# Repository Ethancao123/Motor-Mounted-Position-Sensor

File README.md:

# AS5048B Motor Mount
 AS5048 Breakout PCB for 18XX - 20XX Brushless motors

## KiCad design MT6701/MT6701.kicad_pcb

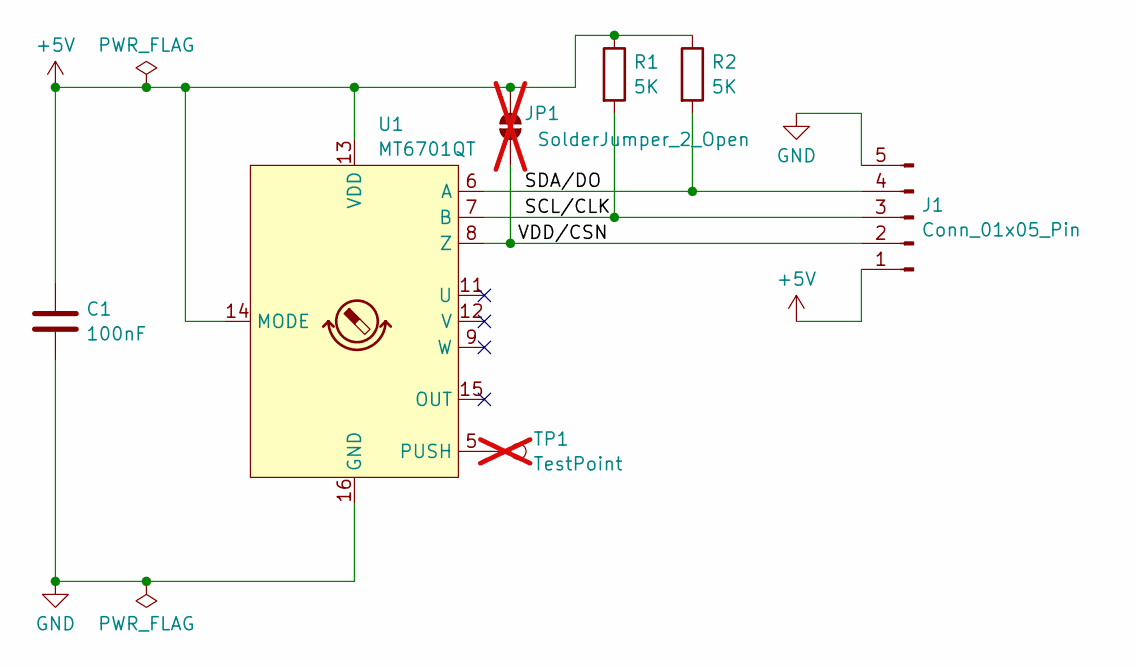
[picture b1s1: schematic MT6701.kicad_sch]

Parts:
C1: 100nF; C_0402_1005Metric; LCSC Part Number C1525
J1: Conn_01x05_Pin; JST_GH_SM05B-GHS-TB_1x05-1MP_P1.25mm_Horizontal; LCSC Part Number C189896
JP1: SolderJumper_2_Open; SolderJumper-2_P1.3mm_Open_TrianglePad1.0x1.5mm; not fitted
R1, R2: 5K; R_0402_1005Metric; LCSC Part Number C25905
TP1: TestPoint; TestPoint_Pad_1.0x1.0mm; not fitted
U1: MT6701QT; QFN-16-1EP_3x3mm_P0.5mm_EP1.7x1.7mm; LCSC Part Number C2913974

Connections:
+5V: C1.1, J1.1, JP1.2 (B), R1.1, R2.1, U1.13 (VDD), U1.14 (MODE)
/SCL/CLK: J1.3, R1.2, U1.7 (B)
/SDA/DO: J1.4, R2.2, U1.6 (A)
/VDD/CSN: J1.2, JP1.1 (A), U1.8 (Z)
GND: C1.2, J1.5, J1.MP, U1.16 (GND), U1.17 (GND)
unnamed: TP1.1, U1.5 (PUSH)

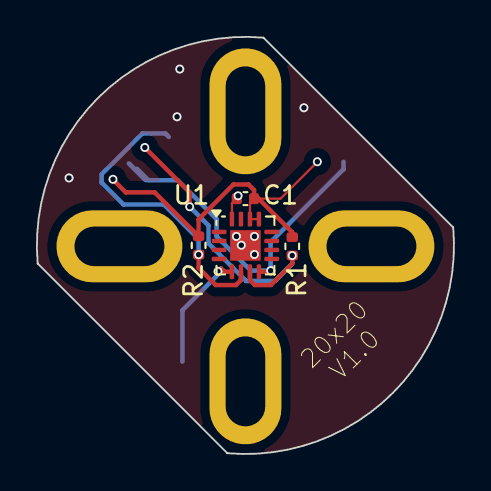
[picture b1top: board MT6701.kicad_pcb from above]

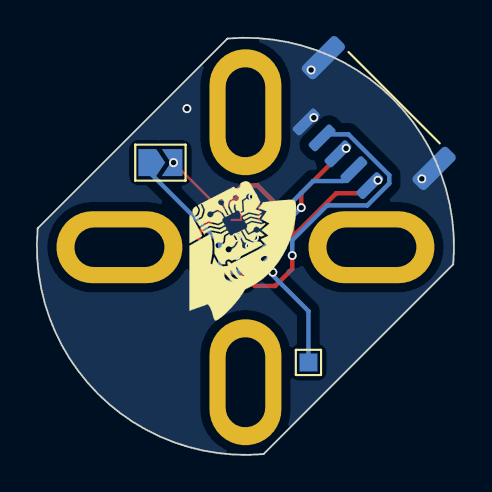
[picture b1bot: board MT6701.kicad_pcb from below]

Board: 2 copper layers, 23.2 x 23.2 mm, 7 parts (3 on the bottom side), 6 nets.

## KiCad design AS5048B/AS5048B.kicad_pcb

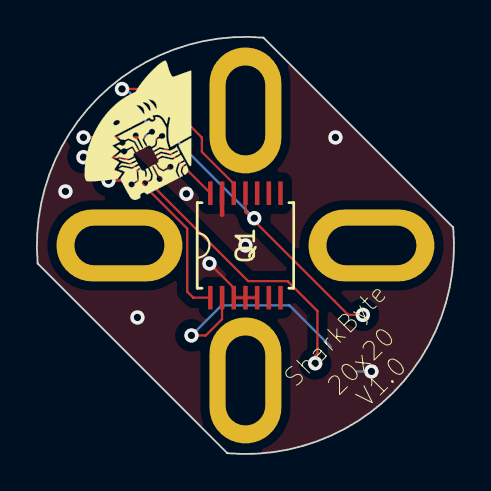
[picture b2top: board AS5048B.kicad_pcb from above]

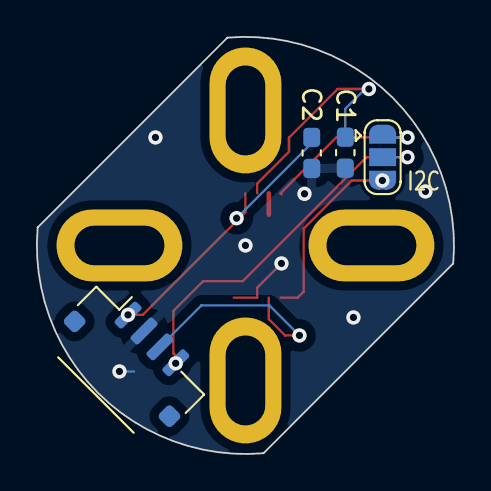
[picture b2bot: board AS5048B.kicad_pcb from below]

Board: 2 copper layers, 23.2 x 23.2 mm, 5 parts (4 on the bottom side), 7 nets.

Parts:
C1: 10uF; C_0603_1608Metric_Pad1.08x0.95mm_HandSolder
C2: 100nF; C_0603_1608Metric_Pad1.08x0.95mm_HandSolder
JP1: SolderJumper_3_Open; SolderJumper-3_P1.3mm_Open_RoundedPad1.0x1.5mm
Je: Conn_01x04_Socket; JST_GH_SM04B-GHS-TB_1x04-1MP_P1.25mm_Horizontal
Q1: AS5048B-HTSP-500; TRANS_HTSP-500_AMS

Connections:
+5V: C2.1, Je.1, Q1.11 (VDD5V)
/I2C: JP1.3 (B), Q1.1 (SDA)
/PWM: JP1.1 (A), Q1.14 (PWM)
GND: C1.1, C2.2, Je.2, Q1.3 (A2), Q1.4 (A1), Q1.5 (TEST), Q1.13 (GND)
unnamed: Je.3, Q1.2 (SCL)
unnamed: JP1.2 (C), Je.4
unnamed: C1.2, Q1.12 (VDD3V)

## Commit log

2024-01-08 [ImgBot] Optimize images
    *Total -- 113.09kb -> 75.46kb (33.27%)
    /pcbback.png -- 56.71kb -> 37.63kb (33.65%)
    /pcbfront.png -- 56.38kb -> 37.84kb (32.89%)
2024-01-13 Added Production Files
2024-01-20 Added 3D Models
2024-06-03 Upgrade to KiCAD 8.0
2024-06-03 Added Text
2024-06-22 Updated Logo
2024-06-22 Renamed Files
2024-06-23 Updated Schematic
2024-07-19 V1 Order
2025-01-28 Added Images
